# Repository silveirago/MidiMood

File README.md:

# MidiMood

For a detailed tutorial, visit: 

- Making Music with Arduino: https://go.musiconerd.com/making-music-with-arduino
- Curso Fazendo Música com Arduino em Português: https://go.musiconerd.com/curso-completo
- Build process video: https://youtu.be/aLhOO-UiMg4

This repository contains the code for a custom MIDI controller project called MidiMood, built using an ATmega32U4 microcontroller (or similar). The project is designed to handle potentiometers, buttons, and other controls to send MIDI messages via USB, BLE, or standard MIDI protocols.

## Table of Contents

- [Overview](#overview)
- [Features](#features)
- [Files Description](#files-description)
- [Setup Instructions](#setup-instructions)
- [Dependencies](#dependencies)
- [Usage](#usage)
- [License](#license)

## Overview

MidiMood is a comprehensive MIDI controller implementation that supports various input methods (buttons, potentiometers, encoders) and output methods (USB MIDI, BLE MIDI). The controller is designed to be highly customizable, supporting multiple microcontroller platforms including ATmega32U4, ATmega328, and Teensy.

## Features

- **USB MIDI Support**: Send and receive MIDI messages over USB.
- **BLE MIDI Support**: Use Bluetooth Low Energy (BLE) for wireless MIDI communication.
- **Potentiometer and Button Handling**: Capture input from potentiometers and buttons and convert them into MIDI messages.
- **Multiplexer Support**: Extend the number of inputs using multiplexers.
- **Debugging Support**: Debugging messages can be enabled via serial communication.
- **Multi-platform**: Supports ATmega32U4, ATmega328, and Teensy microcontrollers.

## Files Description

- **_MidiMood.ino**: The main Arduino sketch that initializes the MIDI controller and runs the main loop.
- **A_POTENTIOMETERS.ino**: Contains the logic for reading potentiometer values and converting them into MIDI Control Change messages.
- **B_BUTTONS.ino**: Handles the button inputs, converting them into MIDI Note On/Off or Control Change messages.
- **FUNCTIONS.ino**: Helper functions used throughout the project, including handling MIDI messages and other utility functions.
- **LOOP.ino**: The main loop where the program checks for inputs and sends out MIDI messages.
- **MACKIE.h**: Defines constants for Mackie Control Universal (MCU) protocol, used for controlling DAWs.
- **Z_ATMEGA32U4.ino**: Microcontroller-specific setup code for ATmega32U4-based boards.
- **Z_SETUP.ino**: General setup code, initializing pins, and configuring input/output modes.

## Material

* Arduino Pro Micro: https://amzn.to/2Vcz3Nz
* Wires: https://amzn.to/2xugvPF
* Bare Copper Wire (optional) 18-24-gauge: https://amzn.to/2FVuDpe
* 26 Rotary potentiometer b10k: https://amzn.to/3ckRKUY
* 26 Knobs
* Spacers M3 35mm: https://amzn.to/2z15BkN
* M3 screws: https://amzn.to/2RHtfJw
* Multiplexer CD4067: https://amzn.to/303jJVe
* 11 Toggle switch: https://amzn.to/3hDmORR
* 1 led
* 1 led support
* 1 resistor 1k ohm

## Setup Instructions

### 1. Clone the Repository

```bash
git clone https://github.com/yourusername/midi-controller-project.git
cd midi-controller-project
```

### 2. Install Arduino IDE

Make sure you have the Arduino IDE installed on your computer. You can download it from the [official website](https://www.arduino.cc/en/software).

### 3. Open the Project

Open the `_MidiMood.ino` file in the Arduino IDE. This file serves as the entry point to the project.

### 4. Select Your Board

In the Arduino IDE, select the appropriate board based on your microcontroller:
- For ATmega32U4 boards (e.g., Arduino Leonardo), select **Arduino Leonardo**.
- For ATmega328 boards (e.g., Arduino Uno), select **Arduino Uno**.
- For Teensy boards, select the correct Teensy model.

### 5. Upload the Code

Connect your microcontroller to your computer via USB and upload the code using the **Upload** button in the Arduino IDE.

## Dependencies

- **ResponsiveAnalogRead**: Library for smoothing analog readings from potentiometers.
- **MIDI Library**: To handle MIDI communication over USB and serial.
- **BLE MIDI**: For Bluetooth MIDI communication (if using BLE).

You can install these libraries using the Arduino Library Manager.

## Usage

Once the code is uploaded, your MIDI controller will be recognized by your computer or mobile device as a MIDI device. You can start using it to send MIDI messages to your DAW or other MIDI-compatible software.

### Debugging

If you want to see debugging messages, enable the `DEBUG` flag in the code. This will allow you to monitor the MIDI messages and other details via the serial monitor in the Arduino IDE.

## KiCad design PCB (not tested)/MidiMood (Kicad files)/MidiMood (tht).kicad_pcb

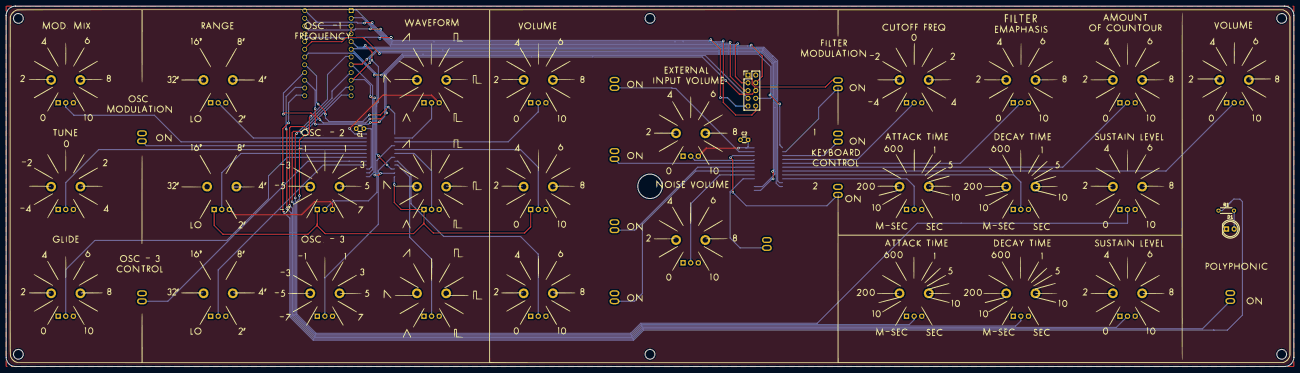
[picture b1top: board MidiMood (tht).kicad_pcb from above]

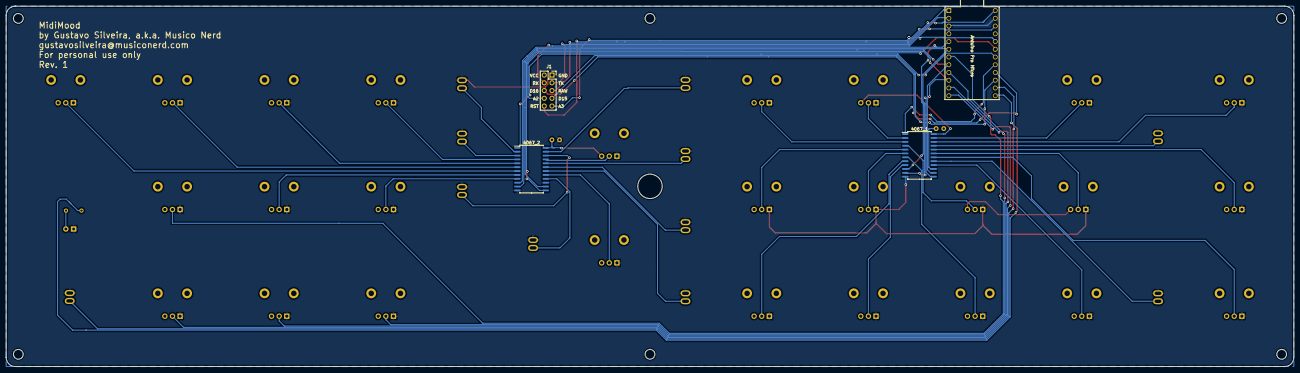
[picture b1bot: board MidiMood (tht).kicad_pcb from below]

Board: 2 copper layers, 422.4 x 118.2 mm, 45 parts (3 on the bottom side), 55 nets.

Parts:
4067_1, 4067_2: CD74HC4067M; SOIC-24W_7.5x15.4mm_P1.27mm
C1, C2: 100nF; C_Disc_D3.0mm_W1.6mm_P2.50mm
D1: LED; LED_D5.0mm
J1: Connector; PinHeader_2x05_P2.54mm_Vertical
R1: 220OHMS; R_Axial_DIN0204_L3.6mm_D1.6mm_P5.08mm_Horizontal
SW1, SW2, SW3, SW4, SW5, SW6, SW7, SW8, SW9, SW10, SW11: SW; Toggle switch small
U3: Arduino_Pro_Micro; ProMicro
pot1, pot2, pot3, pot4, pot5, pot6, pot7, pot8, pot9, pot10, pot11, pot12, pot13, pot14, pot15, pot16, pot17, pot18, pot19, pot20, pot21, pot22, pot23, pot24, pot25, pot26: 10k; Potentiometer_Alpha_RD901F-40-00D_Single_Vertical_CircularH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

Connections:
/A2: J1.8, U3.19
/A3: J1.9, U3.20
/D15: J1.7, U3.16
/D16: J1.6, U3.15
/RAW: J1.5, U3.24
/RST: J1.10, U3.22
/RX: J1.4, U3.2
/S0: 4067_1.10, 4067_2.10, U3.5
/S1: 4067_1.11, 4067_2.11, U3.6
/S2: 4067_1.14, 4067_2.14, U3.8
/S3: 4067_1.13, 4067_2.13, U3.10
/SIG_1: 4067_1.1, U3.17
/SIG_2: 4067_2.1, U3.18
/TX: J1.3, U3.1
/led: R1.1, U3.13
/mux_0: 4067_1.9, pot11.2
/mux_0-2: 4067_2.9, pot18.2
/mux_1: 4067_1.8, pot14.2
/mux_1-2: 4067_2.8, pot21.2
/mux_2: 4067_1.7, pot8.2
/mux_2-2: 4067_2.7, pot26.2
/mux_3: 4067_1.6, pot10.2
/mux_3-2: 4067_2.6, pot23.2
/mux_4: 4067_1.5, pot13.2
/mux_4-2: 4067_2.5, pot20.2
/mux_5: 4067_1.4, pot7.2
/mux_5-2: 4067_2.4, pot17.2
/mux_6: 4067_1.3, pot12.2
/mux_6-2: 4067_2.3, SW9.2
/mux_7: 4067_1.2, pot9.2
/mux_7-2: 4067_2.2, SW8.2
/mux_8: 4067_1.23, pot4.2
/mux_8-2: 4067_2.23, SW3.2
/mux_9: 4067_1.22, pot1.2
/mux_9-2: 4067_2.22, SW10.2
/mux_10: 4067_1.21, SW1.2
/mux_10-2: 4067_2.21, pot15.2
/mux_11: 4067_1.20, pot2.2
/mux_11-2: 4067_2.20, SW4.2
/mux_12: 4067_1.19, pot5.2
/mux_12-2: 4067_2.19, SW5.2
/mux_13: 4067_1.18, pot3.2
/mux_13-2: 4067_2.18, SW6.2
/mux_14: 4067_1.17, SW2.2
/mux_14-2: 4067_2.17, pot16.2
/mux_15: 4067_1.16, pot6.2
/mux_15-2: 4067_2.16, SW7.2
/pot_1: U3.7, pot24.2
/pot_2: U3.9, pot19.2
/pot_3: U3.11, pot22.2
/pot_4: U3.12, pot25.2
/sw_1: SW11.2, U3.14
GND: 4067_1.12, 4067_1.15, 4067_2.12, 4067_2.15, C1.1, C2.1, D1.1, J1.1, SW1.1, SW2.1, SW3.1, SW4.1, SW5.1, SW6.1, SW7.1, SW8.1, SW9.1, SW10.1, SW11.1, U3.3, U3.4, U3.23, pot1.1, pot2.1, pot3.1, pot4.1, pot5.1, pot6.1, pot7.1, pot8.1, pot9.1, pot10.1, pot11.1, pot12.1, pot13.1, pot14.1, pot15.1, pot16.1, pot17.1, pot18.1, pot19.1, pot20.1, pot21.1, pot22.1, pot23.1, pot24.1, pot25.1, pot26.1
unnamed: D1.2, R1.2
VCC: 4067_1.24, 4067_2.24, C1.2, C2.2, J1.2, U3.21, pot1.3, pot2.3, pot3.3, pot4.3, pot5.3, pot6.3, pot7.3, pot8.3, pot9.3, pot10.3, pot11.3, pot12.3, pot13.3, pot14.3, pot15.3, pot16.3, pot17.3, pot18.3, pot19.3, pot20.3, pot21.3, pot22.3, pot23.3, pot24.3, pot25.3, pot26.3

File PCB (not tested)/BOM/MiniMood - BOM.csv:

Comment,Designator,Footprint,LCSC Part Number
CD74HC4067M,"4067_1,4067_2",Package_SO:SOIC-24W_7.5x15.4mm_P1.27mm,C496123
100nF,"C1,C2",Capacitor_SMD:C_0603_1608Metric,C14663
220OHMS,R1,Resistor_SMD:R_0603_1608Metric_Pad0.98x0.95mm_HandSolder,C21189

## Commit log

2020-09-17 Files added
2020-09-17 readme updated
2020-09-17 schematics added
2020-09-25 schematic updated. Some pins of the mux were missing.
2020-09-26 schematics updated
2020-10-27 enclosure laser cut design now fits Ponoko standarts
2021-01-04 schematic gnd and 5v fixed
2021-01-04 enclosure measures fixed
2021-03-10 Kicad files added
2022-10-11 worong file deleted
2024-04-10 new code added
